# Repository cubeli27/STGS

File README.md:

# STGS
##### See-Through Glass Sensor
## Power management and switching hub 

My wish was to keep this board as reusable as possible as well as have it still flexible enough if in the future conditions where it is supposed to work change. It's safe to say I prioritized the current application for what is intended for over-reusability. The only reason this board exists is that a dear professor of mine wishes to upgrade the glass display in front of the electronics lab but the power bank that powers (currently 2) devices runs out every day and it is tedious to replace it constantly. Also having devices turned on all the time when most of the time no one is looking is unproductive. 

# Problems/Solutions
For aesthetic reasons, the requirement was for the board to be inside the glass display and no wires or parts are outside to turn on the devices. 
My solution for this was a simple yet effective combination of LDR and infra-red led & diode pair. Hence it can be triggered from outside the glass as well as benefiting the whole experience as other students can interact with the display.

The setup is currently supplied by a power bank as there are no outlets in the display. Power banks turn off after a few seconds or more up to 20-30s when not enough current is being drawn usually around 100mA but these values depend on the specific power bank. To overcome this my solution was to use ICM7555 in astable mode with a diode for a duty cycle less than 50%. As my power bank turns off at under ~30 seconds for the sake of having a safety factor the circuit is designed to give a pulse every 21s and drawing about 33mA for 0.7s and this seems to work nicely.  Of course, this feature is only active when the board is powered through USB. There is also a DC Barrel Jack I decided should be available. I thought a power management board should have at least two ways of inputting power. This way if in the future the location of the display changes and there is a wall outlet available the whole display can be powered with a 9V power adapter, as well as giving flexibility if ex. an upcoming student project that will be displayed needs more than 5V. Also, a little safety feature was added an auto selector in case someone accidentally connects both the USB and DC jack so nothing bad will happen. 

Power bank: 10,000mAh 

Average consumption: 4mA

So now instead of changing the power bank every day regardless of visitation, idealistically the power bank should be able to work 2500 hours which is around 100 days. Of course, this is without anyone passing by ever and turning it on, and nothing in the real world is ideal. 

From 1 day to 100 days is two orders of magnitude difference. As already mentioned factors, I am happy with even one order of magnitude, and in case the power bank needs to be changed every 10 days as well as provide an interactive display for visitors it is useful and beneficial. 

The code provided is functional but not optimal, but it works. I will revisit this as soon as I get some time.

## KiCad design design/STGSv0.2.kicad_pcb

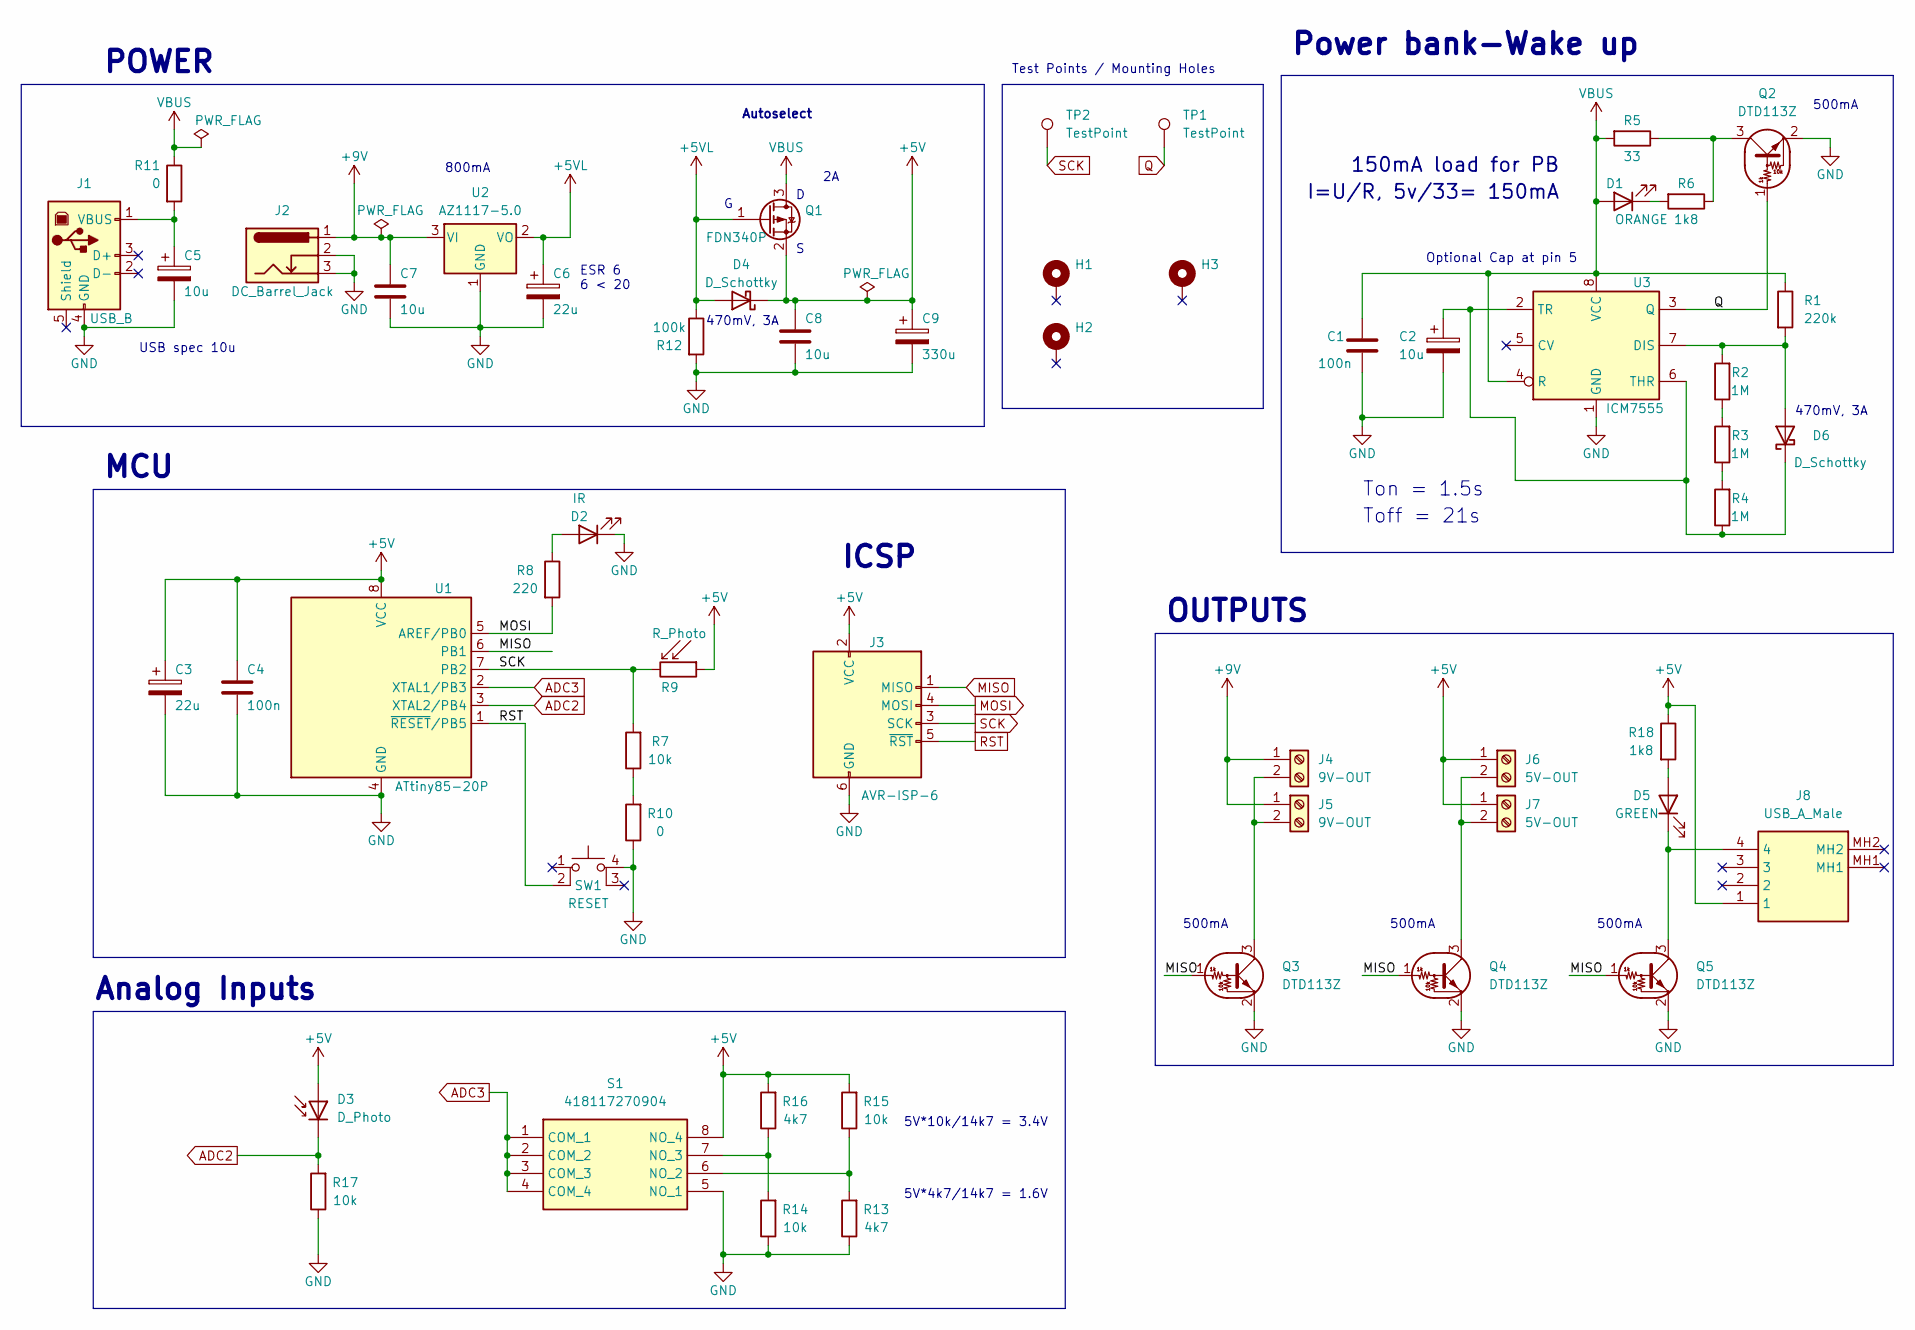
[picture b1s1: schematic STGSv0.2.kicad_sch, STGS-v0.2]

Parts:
C1, C4: 100n; C_1206_3216Metric
C2, C5: 10u; CP_EIA-3216-18_Kemet-A
C3, C6: 22u; CP_EIA-3216-18_Kemet-A
C7, C8: 10u; C_1206_3216Metric
C9: 330u; CP_EIA-7343-31_Kemet-D
D1: ORANGE; LED_1206_3216Metric
D2: IR; LED_D3.0mm
D3: D_Photo; LED_D5.0mm
D4, D6: D_Schottky; D_SMA
D5: GREEN; LED_1206_3216Metric
H1, H2, H3: MountingHole_Pad; MountingHole_2.2mm_M2_DIN965_Pad_TopBottom
J1: USB_B; USB_B_OST_USB-B1HSxx_Horizontal
J2: DC_Barrel_Jack; BarrelJack_GCT_DCJ200-10-A_Horizontal
J3: AVR-ISP-6; PinHeader_2x03_P2.54mm_Vertical
J4, J5: 9V-OUT; 1725656
J6, J7: 5V-OUT; 1725656
J8: USB_A_Male; 480372100; Mouser Part Number 538-48037-2100
Q1: FDN340P; SOT-23
Q2, Q3, Q4, Q5: DTD113Z; SOT-23-3
R1: 220k; R_1206_3216Metric
R2, R3, R4: 1M; R_1206_3216Metric
R5: 33; R_1206_3216Metric
R6, R18: 1k8; R_1206_3216Metric
R7, R14, R15, R17: 10k; R_1206_3216Metric
R8: 220; R_1206_3216Metric
R9: R_Photo; XDCR_PDV-P9003-1
R10, R11: 0; R_1206_3216Metric
R12: 100k; R_1206_3216Metric
R13, R16: 4k7; R_1206_3216Metric
S1: 418117270904; Mouser Part Number 710-418117270904
SW1: RESET; SW_B3SL-1002P_OMR
TP1, TP2: TestPoint; TestPoint_Pad_D2.0mm
U1: ATtiny85-20P; DIP-8_W7.62mm
U2: AZ1117-5.0; SOT-223-3_TabPin2
U3: ICM7555; SOIC-8_3.9x4.9mm_P1.27mm

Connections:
+5V: C3.1, C4.1, C8.1, C9.1, D3.2 (A), D4.1 (K), J3.2 (VCC), J6.1, J7.1, J8.1, Q1.2 (S), R9.1, R15.2, R16.2, R18.1, S1.8 (NO_4), U1.8 (VCC)
+5VL: C6.1, D4.2 (A), Q1.1 (G), R12.1, U2.2 (VO)
+9V: C7.1, J2.1, J4.1, J5.1, U2.3 (VI)
ADC2: D3.1 (K), R17.2, U1.3 (XTAL2/PB4)
ADC3: S1.1 (COM_1), S1.2 (COM_2), S1.3 (COM_3), S1.4 (COM_4), U1.2 (XTAL1/PB3)
GND: C1.2, C2.2, C3.2, C4.2, C5.2, C6.2, C7.2, C8.2, C9.2, D2.1 (K), J1.4 (GND), J2.2, J2.3, J3.6 (GND), Q2.2 (E), Q3.2 (E), Q4.2 (E), Q5.2 (E), R10.1, R12.2, R13.1, R14.1, R17.1, S1.5 (NO_1), SW1.4 (A), U1.4 (GND), U2.1 (GND), U3.1 (GND)
MISO: J3.1 (MISO), Q3.1 (B), Q4.1 (B), Q5.1 (B), U1.6 (PB1)
MOSI: J3.4 (MOSI), R8.2, U1.5 (AREF/PB0)
unnamed: D1.1 (K), R6.2
unnamed: D2.2 (A), R8.1
unnamed: D5.2 (A), R18.2
unnamed: D5.1 (K), J8.4, Q5.3 (C)
unnamed: D6.2 (A), R1.2, R2.2, U3.7 (DIS)
unnamed: C2.1, D6.1 (K), R4.1, U3.2 (TR), U3.6 (THR)
unnamed: C5.1, J1.1 (VBUS), R11.2
unnamed: J4.2, J5.2, Q3.3 (C)
unnamed: J6.2, J7.2, Q4.3 (C)
unnamed: Q2.3 (C), R5.1, R6.1
unnamed: R2.1, R3.2
unnamed: R3.1, R4.2
unnamed: R7.1, R10.2
unnamed: R13.2, R15.1, S1.6 (NO_2)
unnamed: R14.2, R16.1, S1.7 (NO_3)
Q: Q2.1 (B), TP1.1, U3.3 (Q)
RST: J3.5 (~RST), SW1.2, U1.1 (~RESET/PB5)
SCK: J3.3 (SCK), R7.2, R9.2, TP2.1, U1.7 (PB2)
VBUS: C1.1, D1.2 (A), Q1.3 (D), R1.1, R5.2, R11.1, U3.4 (R), U3.8 (VCC)

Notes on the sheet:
500mA
800mA
Ton = 1.5s
Test Points / Mounting Holes
ICSP
Power bank-Wake up
5V*10k/14k7 = 3.4V
I=U/R, 5v/33= 150mA
Autoselect
POWER
Toff = 21s
470mV, 3A
ESR 6 6 < 20
OUTPUTS
150mA load for PB
5V*4k7/14k7 = 1.6V
Analog Inputs
MCU
USB spec 10u
Optional Cap at pin 5

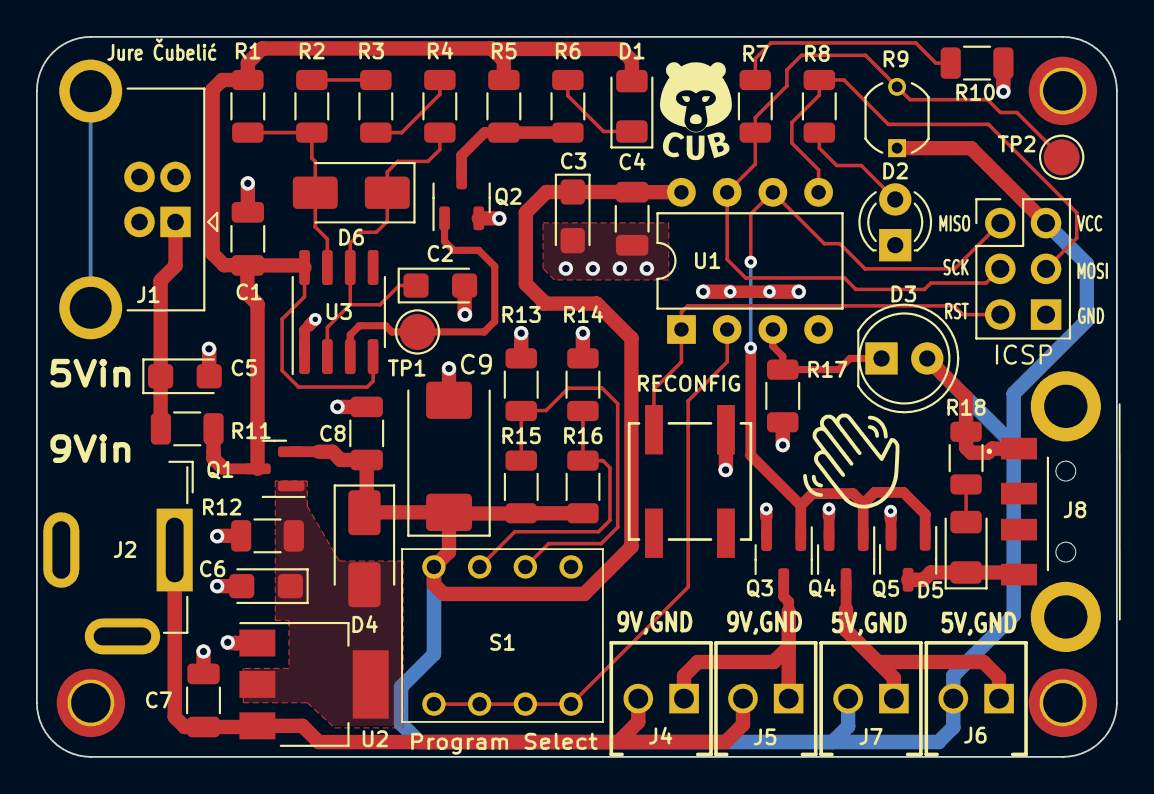
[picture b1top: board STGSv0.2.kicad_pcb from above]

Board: 2 copper layers, 60.0 x 40.0 mm, 56 parts (0 on the bottom side), 27 nets.

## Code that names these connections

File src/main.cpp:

#include<avr/io.h>
#include<avr/interrupt.h>
#include<util/delay.h>
#include <avr/sleep.h>

volatile uint16_t ontime = 0; 
volatile uint16_t proximity = 0;

void init() {
    DDRB |= (1 << PB1); // (ON SWITCH NPN)
    DDRB |= (1 << PB0); // (IR LED)
    DDRB &= ~(1 << PB2); // Interupt pin
    ADCSRA &= ~(1 << ADEN); // Disable ADC

}

void enter_power_down()
{  
  sei();
  MCUCR |= (1 << SM1);      // Enabling powerdown sleep mode, SM[1:0] bits are written to 10
  MCUCR |= (1 << SE);     //Enabling sleep enable bit SLEEP ENABLE
  sleep_cpu();       //__asm__ __volatile__ ( "sleep" "\n\t" :: ); //Sleep instruction in assembly code
}

void enter_idle()
{
  sei();
  MCUCR &= ~(1 << SM1); // Enabling idle sleep mode, SM[1:0] bits are written to 00
  MCUCR |= (1 << SE);     //Enabling sleep enable bit SLEEP ENABLE
  sleep_cpu();           //sleep_mode(); macro might cause race conditions
}

int rxir()
{ // ADC2 for IR reciever
  ADMUX  |= (1 << MUX1) ; //ADC2(PB4) single ended input
  ADCSRA |= (1 << ADEN); // Enable ADC
  ADCSRA |= (1 << ADSC); // Start conversion
  while (ADCSRA & (1 << ADSC)); // Wait for conversion to finish
  return ADC; // Return ADC value 
}
int duration()
{   // ADC3 for potentiometer
  ADMUX &= ~(1 << REFS1) | (1 << REFS0); // Vcc a Aref
  ADMUX = (1 << MUX0) | (1 << MUX1); // Use ADC3 as input
  ADCSRA |= (1 << ADEN); // Enable ADC
  ADCSRA |= (1 << ADSC); // Start conversion
  while (ADCSRA & (1 << ADSC)); // Wait for conversion to finish
  ADMUX = 0x00; // Clears all bits in ADMUX, effectively disabling specific channel selection
  return ADC; // Return ADC value
}

int main(void)
{
  init(); // Initialize the pins
  ontime = duration(); // done only once during startup
  
  while(1){
    PORTB |= (1 << PB0); // IR Led ON
    _delay_ms(100);
    proximity = rxir();
    if(proximity > 300){
      PORTB |= (1<<PB1);      //Turn ON SWITCH
      PORTB &= ~(1 << PB0);   //Turn OFF IR
      for(uint16_t i=0;i < ontime;i++){ // Duration  //TODO Program Select
        _delay_ms(20);
      }
    }
    PORTB &= ~(1 << PB0);   //Turn OFF IR 
    PORTB &= ~(1 << PB1);   //Turn OFF SWITCH
    _delay_ms(10);
    if (PORTB &(1 << PB2)){ //conditions = external interupt not available 
      //enter_idle();        // TODO
      //_delay_ms(5000);
    }
    else if(~PORTB &(1 << PB2)){ //PB2 is HIGH or LIGHT = external interrupt available  
      GIMSK |= (1 << INT0); // Enable INT0 external interupt
      enter_power_down();        // configuration for power down sleep mode
      GIMSK &= ~(1 << INT0); //disable INT0 otherwise interupts rxir(); i think
    }
  }
  return 0;
}

ISR (INT0_vect)        // Interrupt service routine (WAKE UP)
{ // 50k home, 2k2 lab, ~10k hallway = photoresistor pullup @ PB2=INT0=PB2,  6k8 final (false positive priority)
  cli();                // dissable global interrupts, good practice?
  MCUCR &= ~(1 << SE);     //Clear sleep bit as per datasheet SLEEP DISABLE
  uint8_t timeoutCounter = 0; // Initialize the counter
  while (~PINB & (1 << PB2) && timeoutCounter<100) // Wait for button release
  {
    _delay_ms(1); // Small delay to control the loop speed
    timeoutCounter++; 
  } 
}

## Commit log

2023-11-08 Create notes
2023-11-08 Update notes
2023-11-08 LICENSE
